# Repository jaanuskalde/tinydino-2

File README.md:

tinydino-2
==========

Smallest Arduino clone possible to make!

2014 Jaanus Kalde
jaanus.tech-thing.org

FEATURES
--------

   * Arduino compatible
   * Smallest size possible (7.4mm x 7.4mm)
   * Auto reset
   * UART
   * SPI
   * 4 analog inputs
   * 1 digital i/o
   * Now with wings! To ease with programming.

BOM (with farnell codes)
------------------------

    QFN28 atmega88 - 1748530
    8MHz resonator - 1615352
    10k 0603 resistor
    1k 0603 resistor
    0603 red led
    100nF 0603 capacitor

Its free - share!

http://creativecommons.org/licenses/by-nc-sa/3.0/

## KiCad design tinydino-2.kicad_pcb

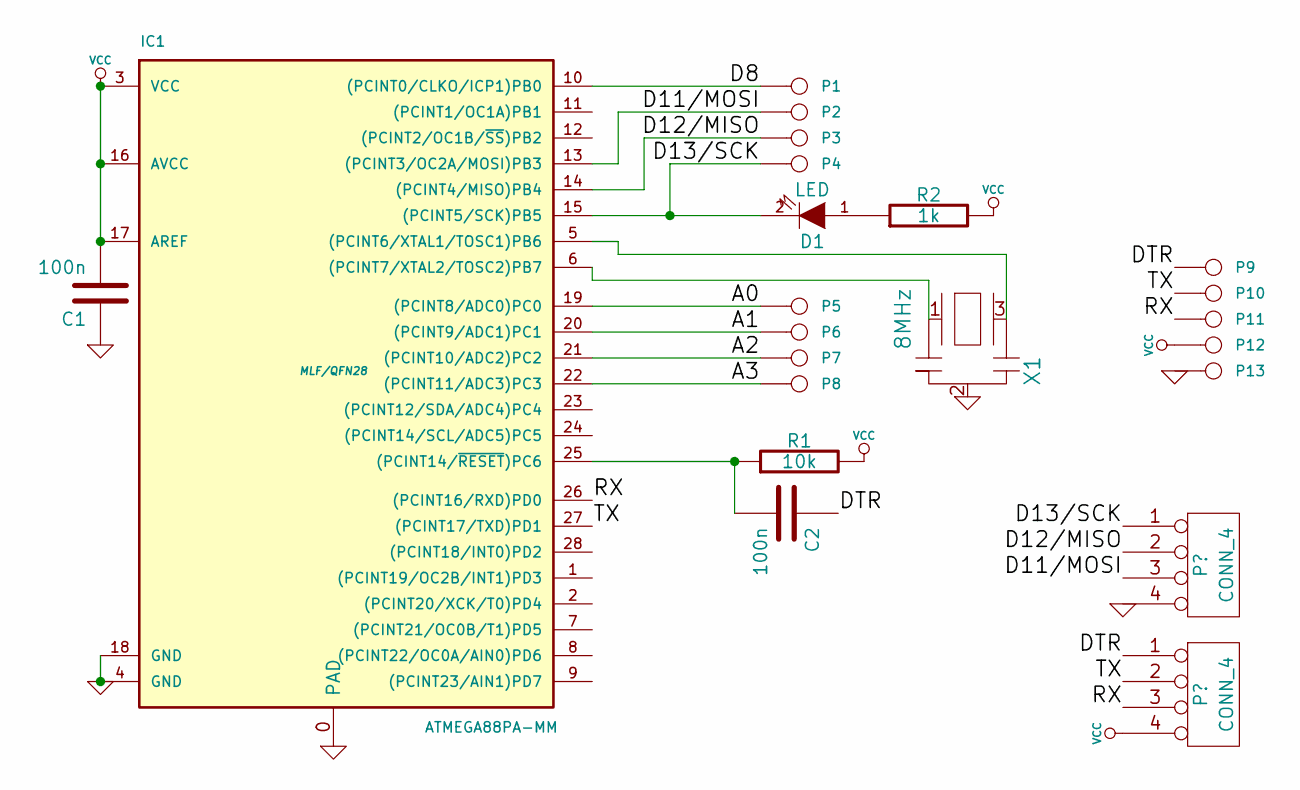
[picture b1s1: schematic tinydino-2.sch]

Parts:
C1, C2: 100n
D1: LED
IC1: ATMEGA88PA-MM; MLF/QFN28
P1, P2, P3, P4, P5, P6, P7, P8, P9, P10, P11, P12, P13: CONN_1
R1: 10k
R2: 1k
X1: 8MHz

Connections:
/A0: IC1.19 ((PCINT8/ADC0)PC0), P5.1
/A1: IC1.20 ((PCINT9/ADC1)PC1), P6.1
/A2: IC1.21 ((PCINT10/ADC2)PC2), P7.1
/A3: IC1.22 ((PCINT11/ADC3)PC3), P8.1
/D8: IC1.10 ((PCINT0/CLKO/ICP1)PB0), P1.1
/D11/MOSI: IC1.13 ((PCINT3/OC2A/MOSI)PB3), P2.1; also elsewhere on the board
/D12/MISO: IC1.14 ((PCINT4/MISO)PB4), P3.1; also elsewhere on the board
/D13/SCK: D1.2 (K), IC1.15 ((PCINT5/SCK)PB5), P4.1; also elsewhere on the board
/DTR: C2.1, P9.1; also elsewhere on the board
/RX: IC1.26 ((PCINT16/RXD)PD0), P11.1; also elsewhere on the board
/TX: IC1.27 ((PCINT17/TXD)PD1), P10.1; also elsewhere on the board
GND: C1.1, IC1.0 (PAD), IC1.4 (GND), IC1.18 (GND), P13.1, X1.2; also elsewhere on the board
unnamed: IC1.5 ((PCINT6/XTAL1/TOSC1)PB6), X1.3
unnamed: IC1.6 ((PCINT7/XTAL2/TOSC2)PB7), X1.1
unnamed: C2.2, IC1.25 ((PCINT14/~RESET~)PC6), R1.1
unnamed: D1.1 (A), R2.1
VCC: C1.2, IC1.3 (VCC), IC1.16 (AVCC), IC1.17 (AREF), P12.1, R1.2, R2.2; also elsewhere on the board

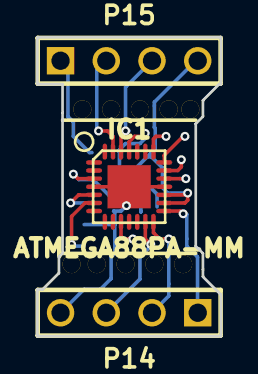
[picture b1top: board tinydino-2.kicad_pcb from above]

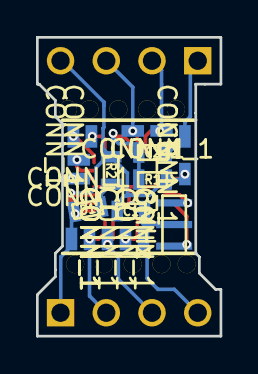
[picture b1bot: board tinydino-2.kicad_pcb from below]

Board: 2 copper layers, 10.2 x 16.6 mm, 32 parts (19 on the bottom side), 17 nets.

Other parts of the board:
P14, P15: CONN_4; conn_4
drill_1mm, drill_1mm#2, drill_1mm#3, drill_1mm#4, drill_1mm#5, drill_1mm#6, drill_1mm#7, drill_1mm#8, drill_1mm#9, drill_1mm#10: VAL**; drill_1mm

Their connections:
/D11/MOSI: P14.3; also elsewhere on the board
/D12/MISO: P14.2; also elsewhere on the board
/D13/SCK: P14.1; also elsewhere on the board
/DTR: P15.1; also elsewhere on the board
/RX: P15.3; also elsewhere on the board
/TX: P15.2; also elsewhere on the board
GND: P14.4; also elsewhere on the board
VCC: P15.4; also elsewhere on the board

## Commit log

2014-05-02 ver1
2014-05-02 readme update
2014-05-03 New readme
